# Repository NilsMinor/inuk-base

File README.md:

# Inuk base

This board is used in my open source smart garden light project. It is a 2 layer 70 mm x 100 mm design and serves as an NRF52 module carrier.
The board is powered by one 18650 rechargeable lipo and charged by an TP4056 module with a 6V solar cell. The light interface can controll up to five pwm controlled 3W LEDs.

#### Pin description

| Pin   |  Function  |                    Note |
| ----- | :--------: | ----------------------: |
| P0.26 |   LED D2   |             high active |
| P0.27 |   LED D3   |             high active |
| P0.25 | BUTTON SW2 |              low active |
| P0.06 |  UART TX   |                         |
| P0.08 |  UART RX   |                         |
| P0.07 |  UART RTS  |                         |
| P0.05 |  UART CTS  |                         |
| P0.02 |    AIN0    |     analog input - VBAT |
| P0.03 |    AIN1    |   analog input - VSOLAR |
| P0.04 |    AIN2    |            analog input |
| P0.28 |    AIN4    |     analog input - VLDR |
| P0.29 |    AIN5    |            analog input |
| P0.30 |    AIN6    |            analog input |
| P0.31 |    AIN7    |            analog input |
| P0.11 |    LIO1    |        pwm output led 1 |
| P0.12 |    LIO2    |        pwm output led 2 |
| P0.13 |    LIO3    |        pwm output led 3 |
| P0.14 |    LIO4    |        pwm output led 4 |
| P0.15 |    LIO5    |        pwm output led 5 |
| P0.16 | PIR INPUT  | pir input - high active |

#### Software

The inuk-base board is equipped with an E73-2G4M04S1B module that contains an nrf52832 SoC from nordic semiconductor. The nrf52832 bluetooth SoC comes with cortex-m4, 64K RAM and 512K ROM.

##### Note

It might happen that the E73 module comes with locked UICR. In order to unlock the flash download nrfjprog from nordic. Run the following command:

```
nrfjprog --recover
```

The output should then look like :

```
Recovering device. This operation might take 30s.
Erasing user code and UICR flash areas.
```

###### Click on the image below to see the gerber files

###### Needs to be changed for version 2

- Remove direct GND connection poligons on E73 module. The direct GND connection is difficult to solder and needs
- Add (+) symbol to battery connector
- The DCDC on the NRF52 module is not supported, this should be changed in the next version.

##View in 3D

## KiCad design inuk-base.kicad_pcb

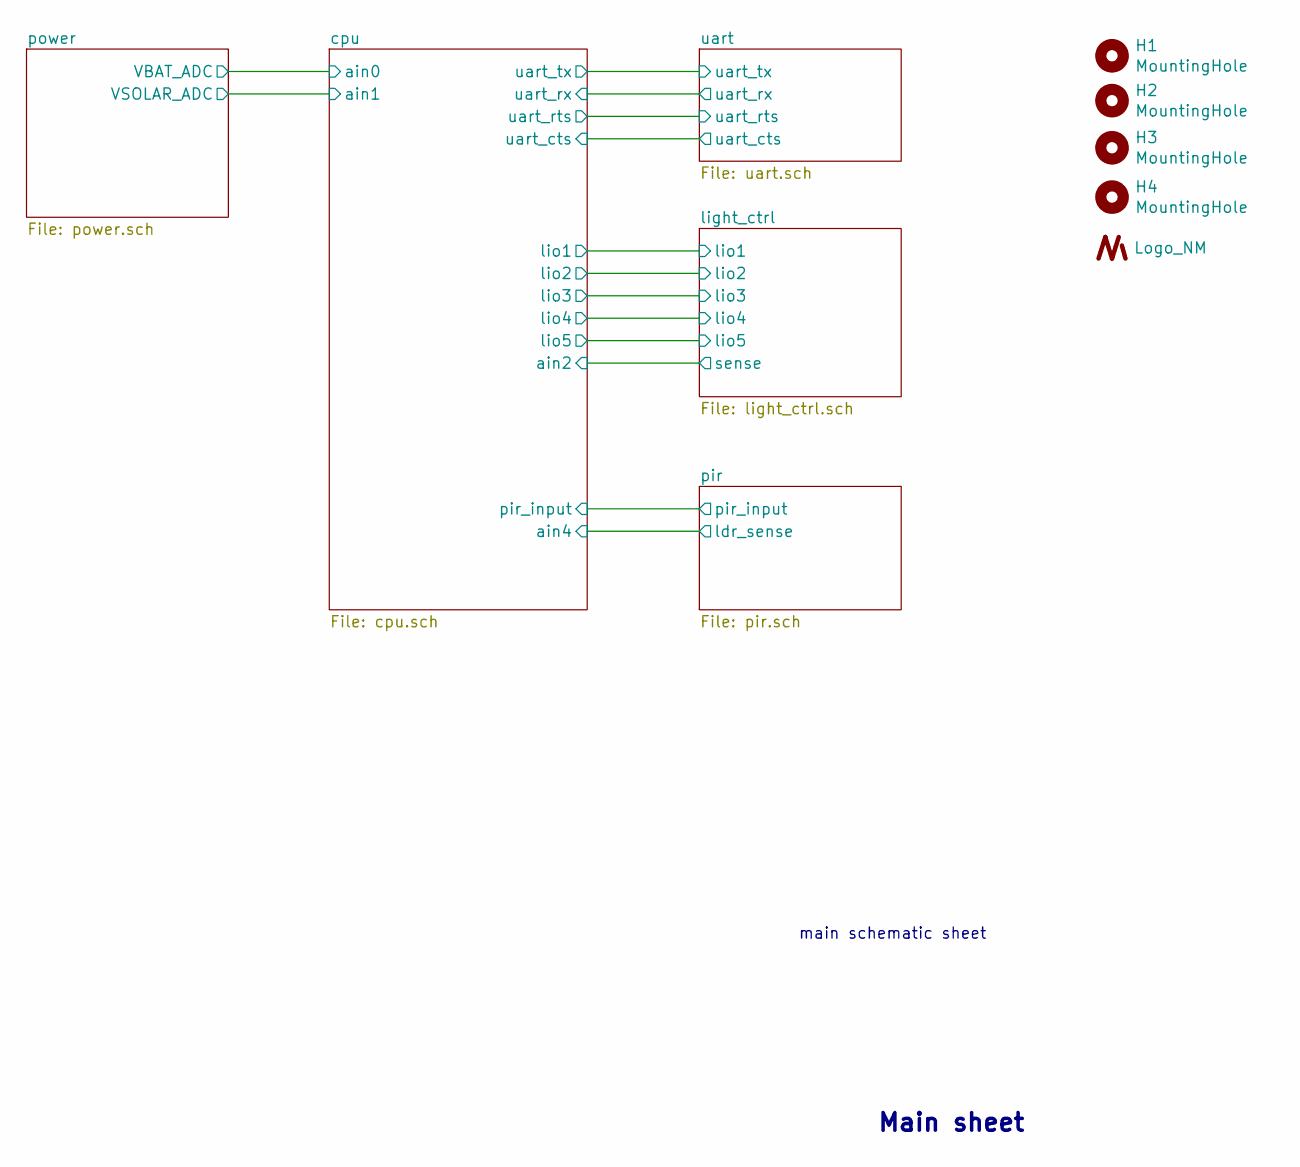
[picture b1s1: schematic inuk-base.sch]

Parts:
H1, H2, H3, H4: MountingHole; MountingHole_3.2mm_M3_Pad_Via
U4: Logo_NM

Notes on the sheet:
Main sheet
main schematic sheet

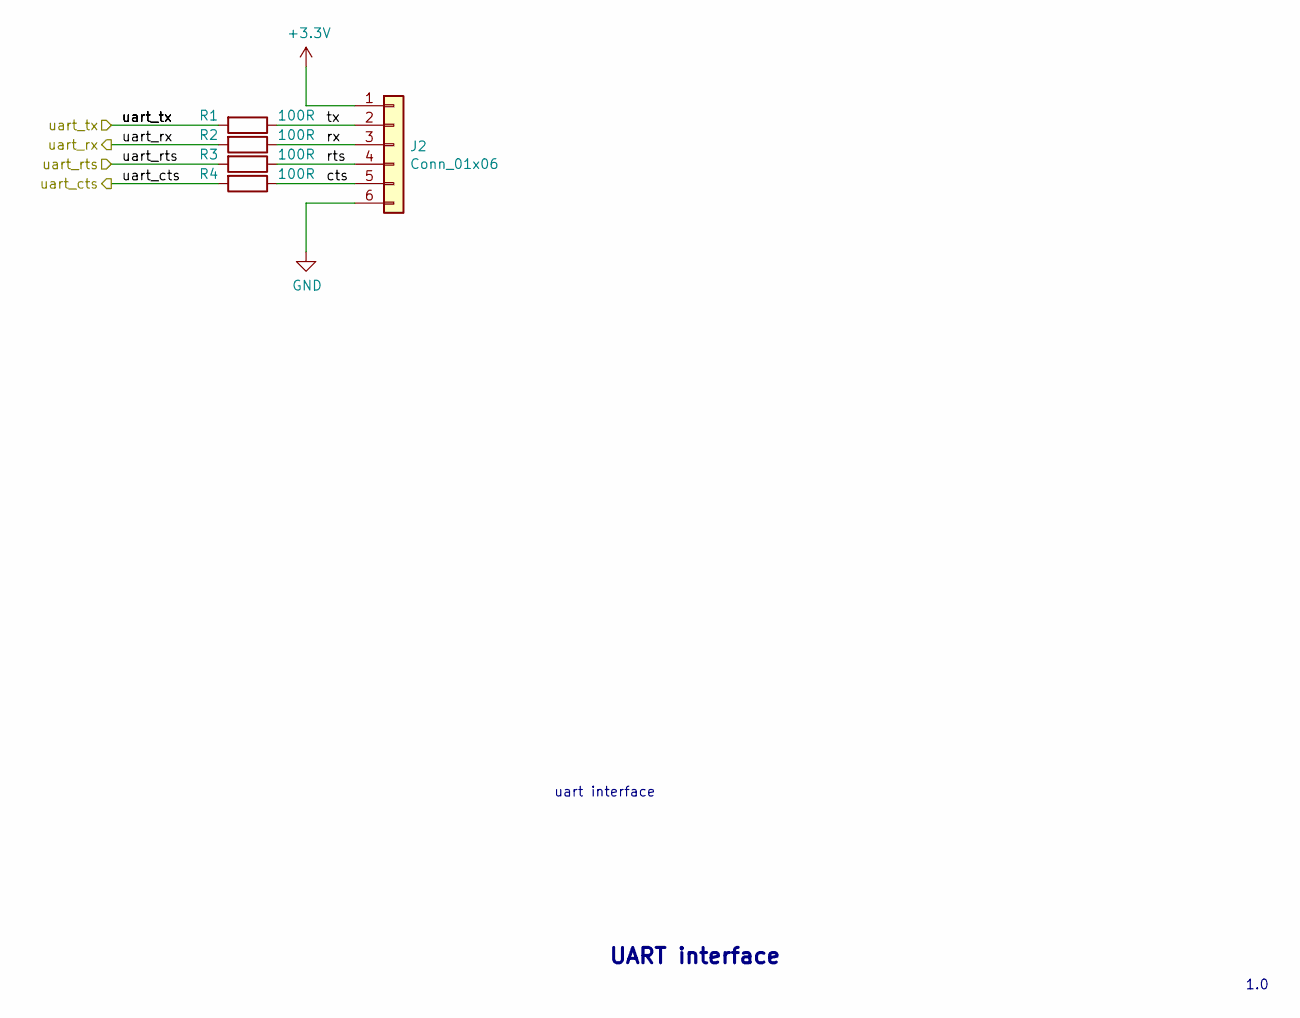
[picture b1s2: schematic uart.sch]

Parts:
J2: Conn_01x06; PinHeader_1x06_P2.54mm_Horizontal
R1, R2, R3, R4: 100R; R_0805_2012Metric_Pad1.15x1.40mm_HandSolder; MPN 0805W8F1000T5E; LCSC C17408

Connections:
/cpu/uart_cts: R4.2; also elsewhere on the board
/cpu/uart_rts: R3.2; also elsewhere on the board
/cpu/uart_rx: R2.2; also elsewhere on the board
/cpu/uart_tx: R1.2; also elsewhere on the board
/uart/cts: J2.5, R4.1
/uart/rts: J2.4, R3.1
/uart/rx: J2.3, R2.1
/uart/tx: J2.2, R1.1

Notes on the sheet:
UART interface
uart interface
1.0

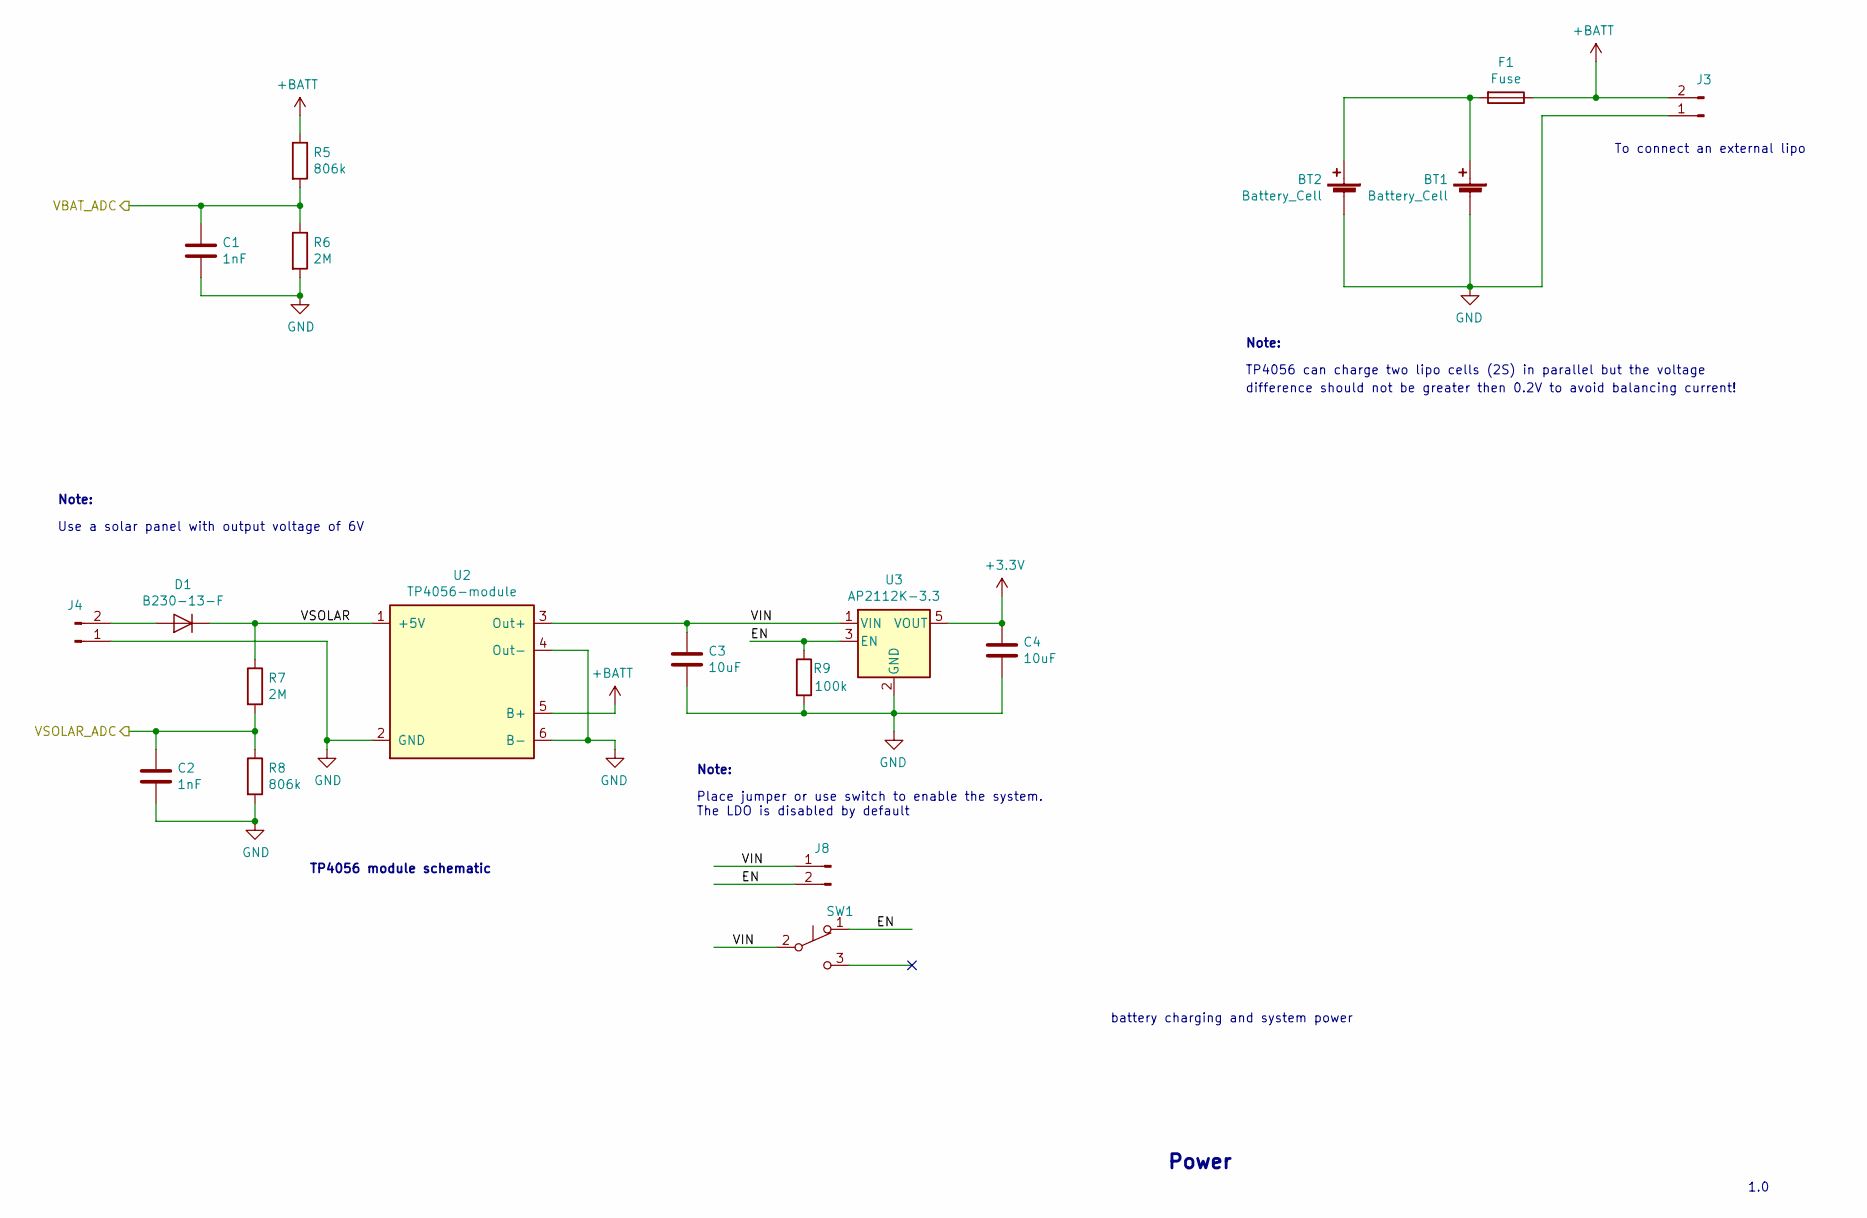
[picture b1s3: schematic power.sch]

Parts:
BT1, BT2: Battery_Cell; BatteryHolder_MPD_BH-18650-PC2
C1, C2: 1nF; C_0805_2012Metric_Pad1.15x1.40mm_HandSolder; MPN CL21B102KBCNNNC; LCSC C46653
C3, C4: 10uF; C_1210_3225Metric_Pad1.42x2.65mm_HandSolder; MPN CL31A106KBHNNNE; LCSC C13585
D1: B230-13-F; D_SMB; MPN B230-13-F; LCSC C110482
F1: Fuse; Fuse_1206_3216Metric; MPN 0466002.NRHF; LCSC C3105
J3, J4: Conn_01x02_Male; JST_PH_S2B-PH-SM4-TB_1x02-1MP_P2.00mm_Horizontal
J8: Conn_01x02_Male; PinHeader_1x02_P2.54mm_Vertical
R5, R8: 806k; R_0805_2012Metric_Pad1.15x1.40mm_HandSolder; MPN 0805W8F8063T5E; LCSC C63494
R6, R7: 2M; R_0805_2012Metric_Pad1.15x1.40mm_HandSolder; MPN 0805W8F2004T5E; LCSC C26112
R9: 100k; R_0805_2012Metric_Pad1.15x1.40mm_HandSolder; MPN 0805W8F1003T5E; LCSC C17407
SW1: SW_Push_SPDT; SW_SPDT_CK-JS102011SAQN
U2: TP4056-module
U3: AP2112K-3.3; SOT-23-5; MPN AP2112K-3.3TRG1; LCSC C51118

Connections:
+BATT: F1.1, J3.2, R5.1, U2.5 (B+); also elsewhere on the board
/power/EN: J8.2, R9.1, SW1.1 (A), U3.3 (EN)
/power/VBAT_ADC: C1.1, R5.2, R6.1; also elsewhere on the board
/power/VIN: C3.1, J8.1, SW1.2 (B), U2.3 (Out+), U3.1 (VIN)
/power/VSOLAR: D1.1 (K), R7.1, U2.1 (+5V)
/power/VSOLAR_ADC: C2.1, R7.2, R8.1; also elsewhere on the board
unnamed: BT1.1 (+), BT2.1 (+), F1.2
unnamed: D1.2 (A), J4.2

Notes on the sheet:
TP4056 can charge two lipo cells (2S) in parallel but the voltage
difference should not be greater then 0.2V to avoid balancing current!
Note:
Place jumper or use switch to enable the system. The LDO is disabled by default
TP4056 module schematic
Use a solar panel with output voltage of 6V
Power
battery charging and system power
To connect an external lipo
1.0

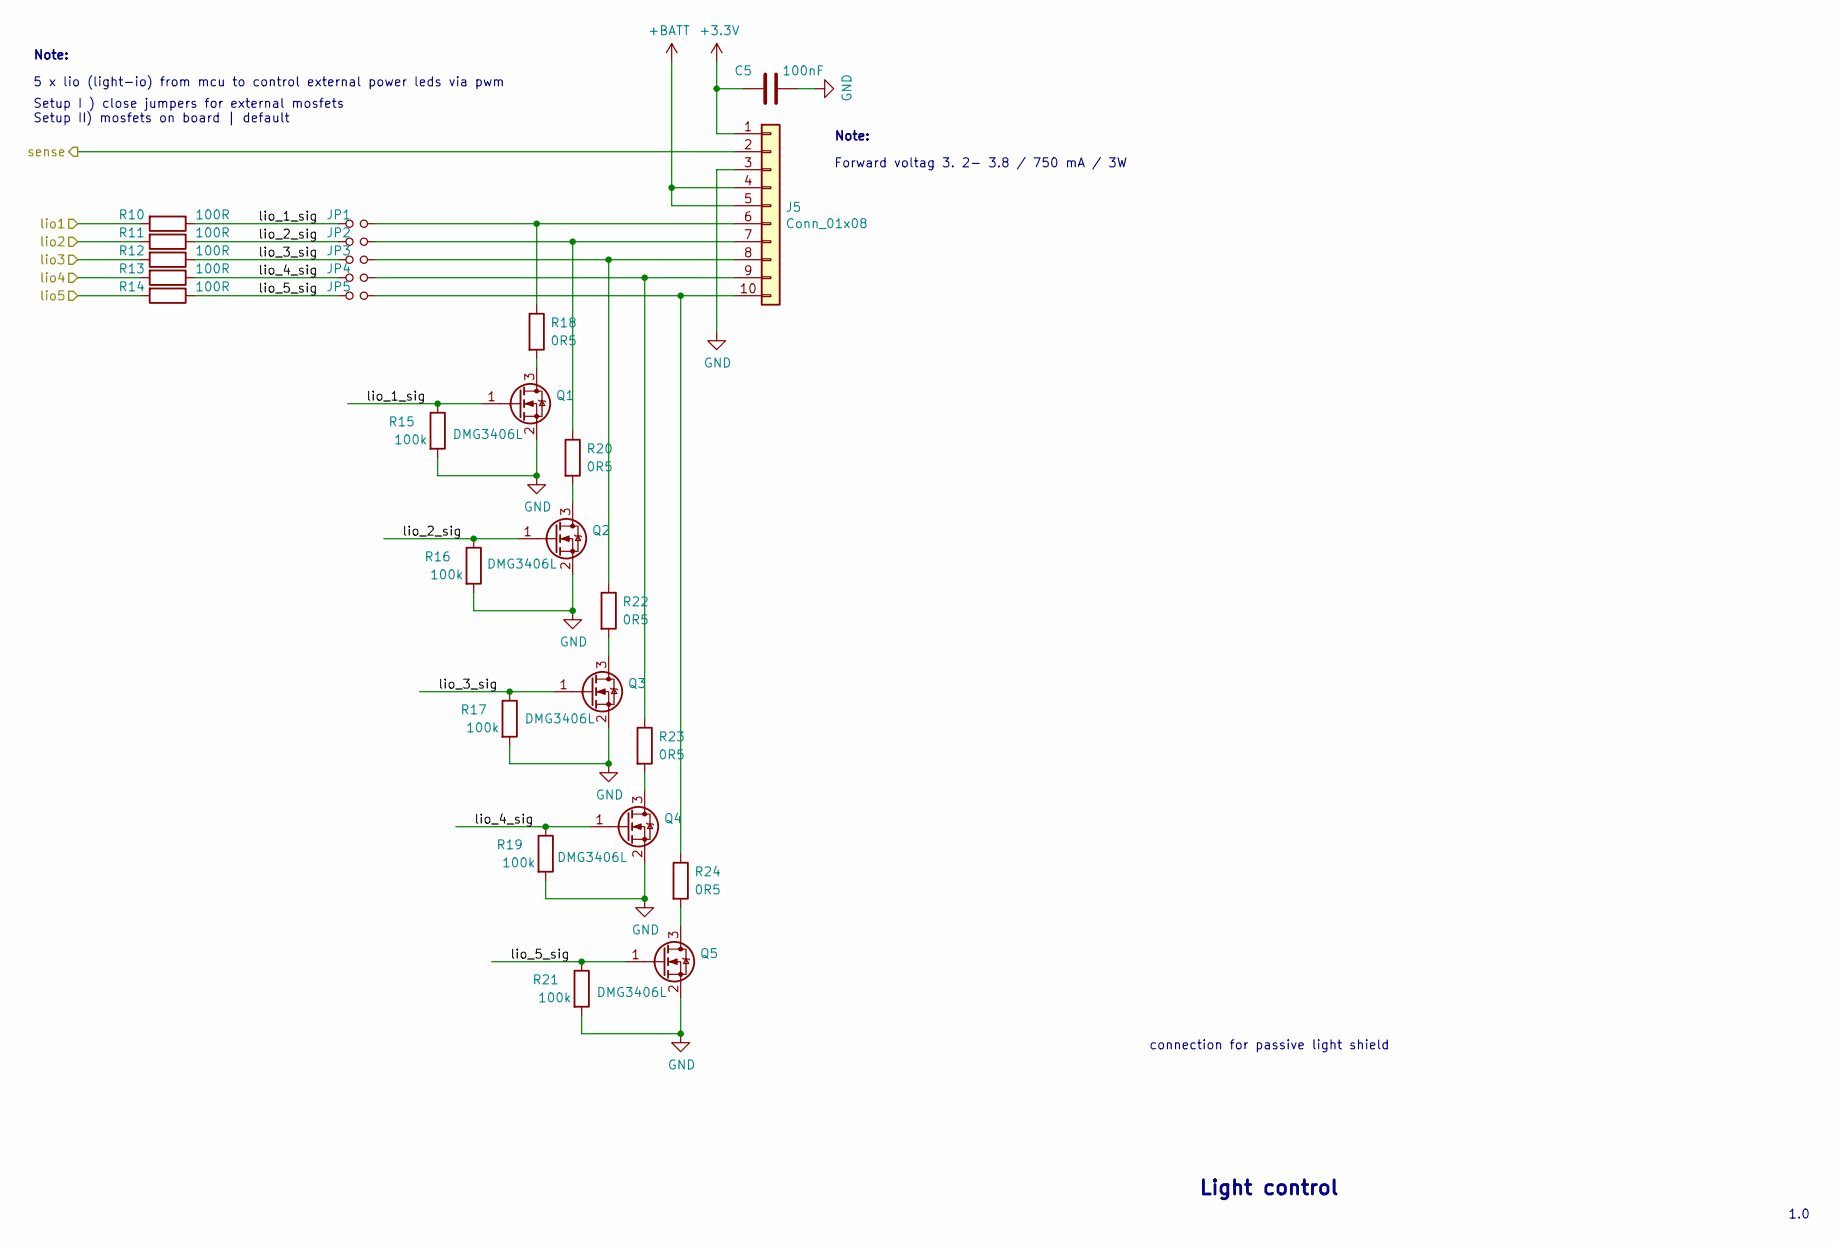
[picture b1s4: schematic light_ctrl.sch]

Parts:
C5: 100nF; C_0805_2012Metric_Pad1.15x1.40mm_HandSolder; MPN CL21B104KCFNNNE; LCSC C28233
J5: Conn_01x08; LED_shield
JP1, JP2, JP3, JP4, JP5: Jumper_NO_Small; SolderJumper-2_P1.3mm_Open_RoundedPad1.0x1.5mm
Q1, Q2, Q3, Q4, Q5: DMG3406L; SOT-23; MPN DMG3420U-7; LCSC C154722
R10, R11, R12, R13, R14: 100R; R_0805_2012Metric_Pad1.15x1.40mm_HandSolder; MPN 0805W8F1000T5E; LCSC C17408
R15, R16, R17, R19, R21: 100k; R_0805_2012Metric_Pad1.15x1.40mm_HandSolder; MPN 0805W8F1003T5E; LCSC C17407
R18, R20, R22, R23, R24: 0R5; R_1210_3225Metric_Pad1.42x2.65mm_HandSolder; MPN 1210W3F500LT5E; LCSC C21355

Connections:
+BATT: J5.4, J5.5; also elsewhere on the board
/cpu/ain2: J5.2; also elsewhere on the board
/cpu/lio1: R10.2; also elsewhere on the board
/cpu/lio2: R11.2; also elsewhere on the board
/cpu/lio3: R12.2; also elsewhere on the board
/cpu/lio4: R13.2; also elsewhere on the board
/cpu/lio5: R14.2; also elsewhere on the board
/light_ctrl/lio_1_sig: JP1.1, Q1.1 (G), R10.1, R15.1
/light_ctrl/lio_2_sig: JP2.1, Q2.1 (G), R11.1, R16.1
/light_ctrl/lio_3_sig: JP3.1, Q3.1 (G), R12.1, R17.1
/light_ctrl/lio_4_sig: JP4.1, Q4.1 (G), R13.1, R19.1
/light_ctrl/lio_5_sig: JP5.1, Q5.1 (G), R14.1, R21.1
unnamed: J5.6, JP1.2, R18.1
unnamed: J5.7, JP2.2, R20.1
unnamed: J5.8, JP3.2, R22.1
unnamed: J5.9, JP4.2, R23.1
unnamed: J5.10, JP5.2, R24.1
unnamed: Q1.3 (D), R18.2
unnamed: Q2.3 (D), R20.2
unnamed: Q3.3 (D), R22.2
unnamed: Q4.3 (D), R23.2
unnamed: Q5.3 (D), R24.2

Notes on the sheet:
5 x lio (light-io) from mcu to control external power leds via pwm
Note:
Forward voltag 3. 2- 3.8 / 750 mA / 3W
Setup I ) close jumpers for external mosfets Setup II) mosfets on board | default
Light control
connection for passive light shield
1.0

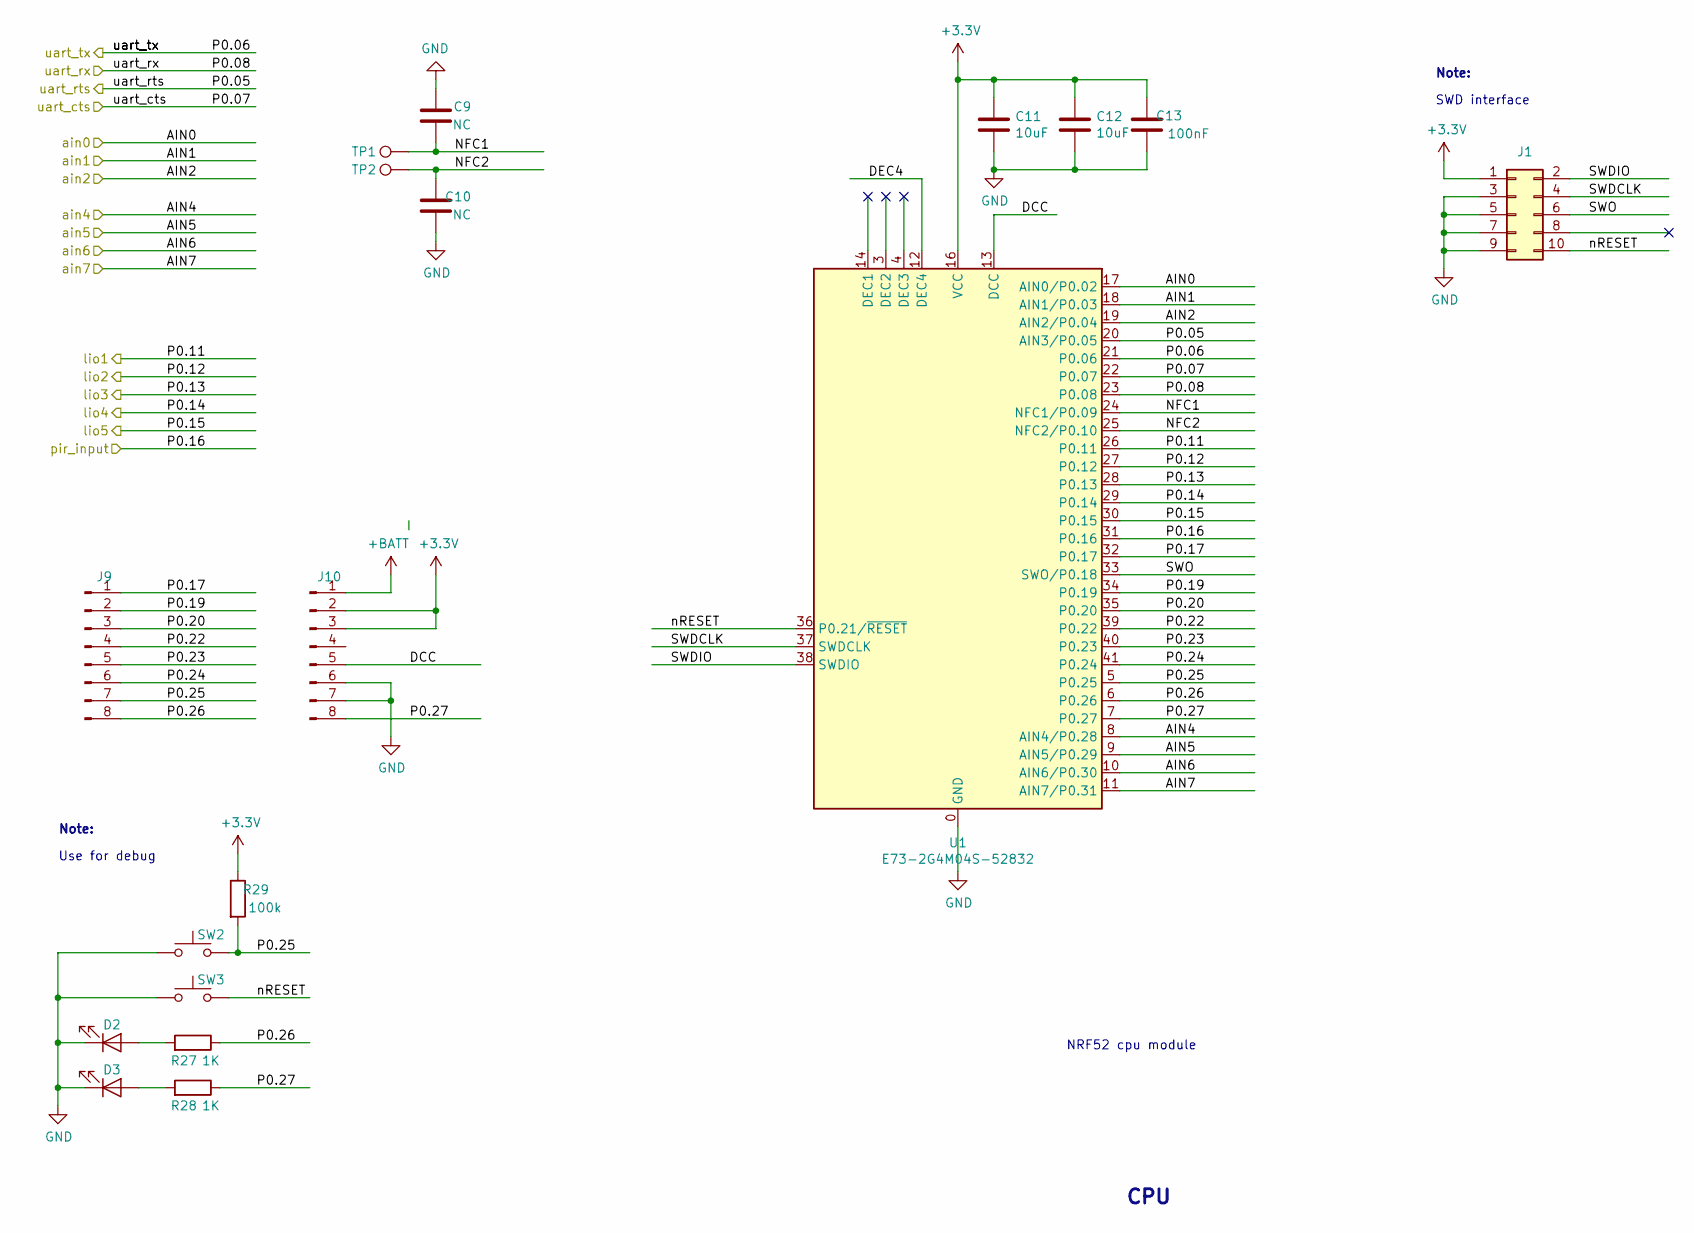
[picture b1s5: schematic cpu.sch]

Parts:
C9, C10: NC; C_0603_1608Metric
C11, C12: 10uF; C_1210_3225Metric_Pad1.42x2.65mm_HandSolder
C13: 100nF; C_0805_2012Metric_Pad1.15x1.40mm_HandSolder
D2, D3: LED; LED_0603_1608Metric_Pad1.05x0.95mm_HandSolder
J1: Conn_02x05_Odd_Even; PinHeader_2x05_P1.27mm_Vertical_SMD
J9, J10: Conn_01x08_Male; PinHeader_1x08_P2.54mm_Vertical_SMD_Pin1Left
R27, R28: 1K; R_0805_2012Metric_Pad1.15x1.40mm_HandSolder
R29: 100k; R_0805_2012Metric_Pad1.15x1.40mm_HandSolder
SW2, SW3: SW_Push; Panasonic_EVQPUL_EVQPUC
TP1, TP2: TestPoint; TestPoint_Pad_D1.5mm
U1: E73-2G4M04S-52832; E73-2G4M04S

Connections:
+BATT: J10.1; also elsewhere on the board
/cpu/AIN6: J10.4, U1.10 (AIN6/P0.30)
/cpu/DCC: J10.5, U1.13 (DCC)
/cpu/DEC4: U1.12 (DEC4)
/cpu/NFC1: C9.2, TP1.1, U1.24 (NFC1/P0.09)
/cpu/NFC2: C10.2, TP2.1, U1.25 (NFC2/P0.10)
/cpu/P0.17: J9.1, U1.32 (P0.17)
/cpu/P0.19: J9.2, U1.34 (P0.19)
/cpu/P0.20: J9.3, U1.35 (P0.20)
/cpu/P0.22: J9.4, U1.39 (P0.22)
/cpu/P0.23: J9.5, U1.40 (P0.23)
/cpu/P0.24: J9.6, U1.41 (P0.24)
/cpu/P0.25: J9.7, R29.2, SW2.2, U1.5 (P0.25)
/cpu/P0.26: J9.8, R27.1, U1.6 (P0.26)
/cpu/P0.27: J10.8, R28.1, U1.7 (P0.27)
/cpu/SWDCLK: J1.4, U1.37 (SWDCLK)
/cpu/SWDIO: J1.2, U1.38 (SWDIO)
/cpu/SWO: J1.6, U1.33 (SWO/P0.18)
/cpu/ain2: U1.19 (AIN2/P0.04); also elsewhere on the board
/cpu/ain4: U1.8 (AIN4/P0.28); also elsewhere on the board
/cpu/lio1: U1.26 (P0.11); also elsewhere on the board
/cpu/lio2: U1.27 (P0.12); also elsewhere on the board
/cpu/lio3: U1.28 (P0.13); also elsewhere on the board
/cpu/lio4: U1.29 (P0.14); also elsewhere on the board
/cpu/lio5: U1.30 (P0.15); also elsewhere on the board
/cpu/nRESET: J1.10, SW3.2, U1.36 (P0.21/~RESET)
/cpu/pir_input: U1.31 (P0.16); also elsewhere on the board
/cpu/uart_cts: U1.22 (P0.07); also elsewhere on the board
/cpu/uart_rts: U1.20 (AIN3/P0.05); also elsewhere on the board
/cpu/uart_rx: U1.23 (P0.08); also elsewhere on the board
/cpu/uart_tx: U1.21 (P0.06); also elsewhere on the board
/power/VBAT_ADC: U1.17 (AIN0/P0.02); also elsewhere on the board
/power/VSOLAR_ADC: U1.18 (AIN1/P0.03); also elsewhere on the board
unnamed: D2.2 (A), R27.2
unnamed: D3.2 (A), R28.2

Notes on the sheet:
SWD interface
Note:
Use for debug
CPU
NRF52 cpu module

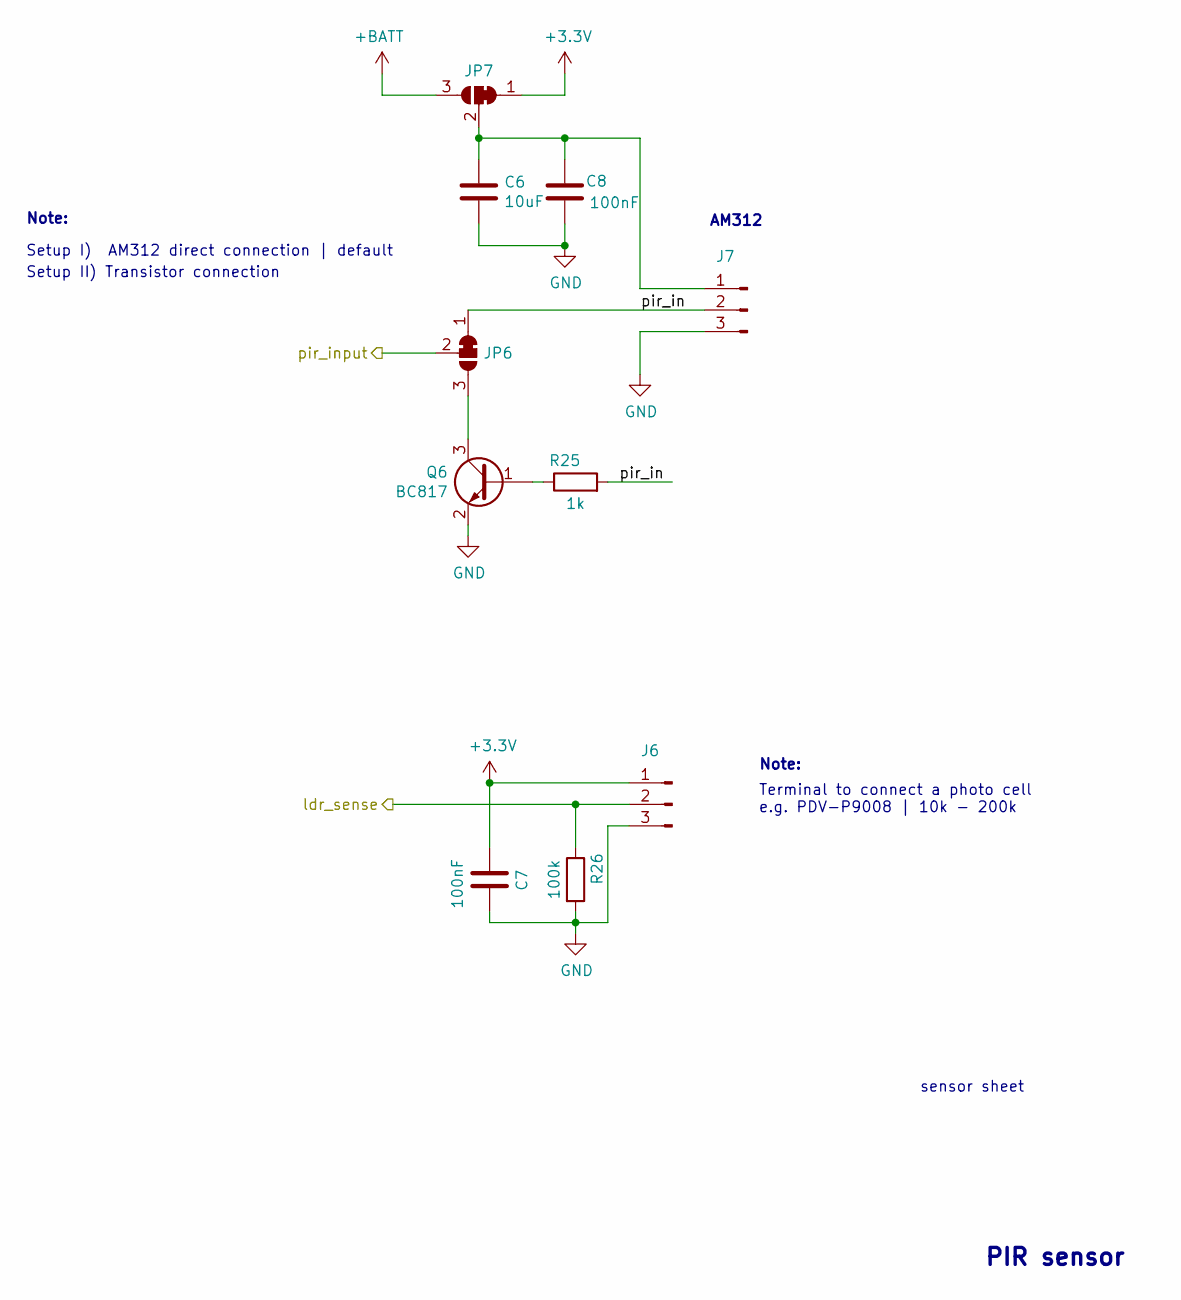
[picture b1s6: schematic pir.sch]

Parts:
C6: 10uF; C_1210_3225Metric_Pad1.42x2.65mm_HandSolder
C7, C8: 100nF; C_0805_2012Metric_Pad1.15x1.40mm_HandSolder
J6, J7: Conn_01x03_Male; PinHeader_1x03_P2.54mm_Vertical
JP6, JP7: SolderJumper_3_Bridged12; SolderJumper-3_P1.3mm_Bridged12_RoundedPad1.0x1.5mm
Q6: BC817; SOT-23
R25: 1k; R_0805_2012Metric_Pad1.15x1.40mm_HandSolder
R26: 100k; R_0805_2012Metric_Pad1.15x1.40mm_HandSolder

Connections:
+BATT: JP7.3 (B); also elsewhere on the board
/cpu/ain4: J6.2, R26.1; also elsewhere on the board
/cpu/pir_input: JP6.2 (C); also elsewhere on the board
/pir/pir_in: J7.2, JP6.1 (A), R25.2
unnamed: C6.1, C8.2, J7.1, JP7.2 (C)
unnamed: JP6.3 (B), Q6.3 (C)
unnamed: Q6.1 (B), R25.1

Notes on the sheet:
Setup I) AM312 direct connection | default
Note:
Setup II) Transistor connection
AM312
Terminal to connect a photo cell e.g. PDV-P9008 | 10k - 200k
PIR sensor
sensor sheet

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
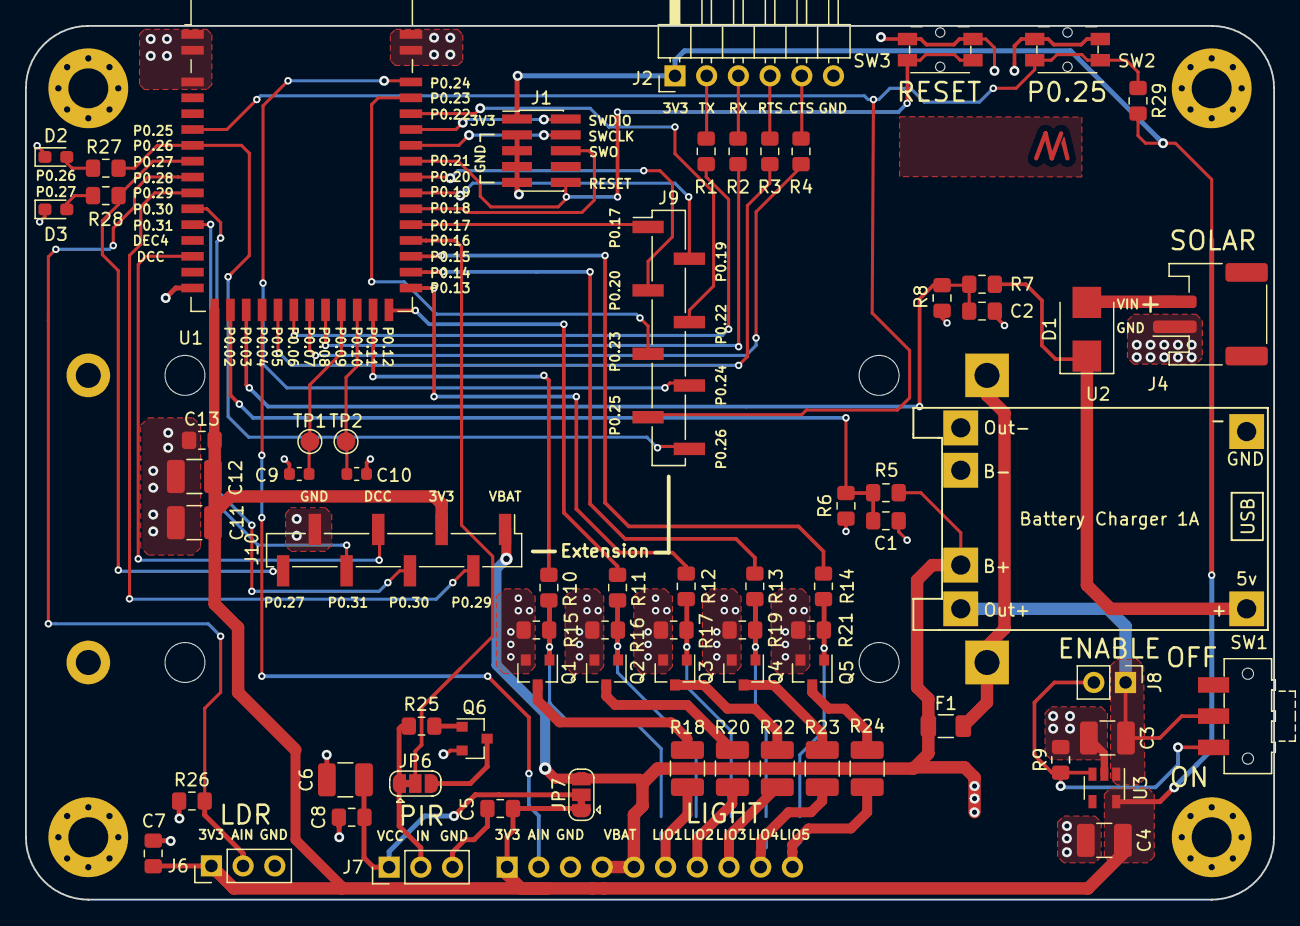
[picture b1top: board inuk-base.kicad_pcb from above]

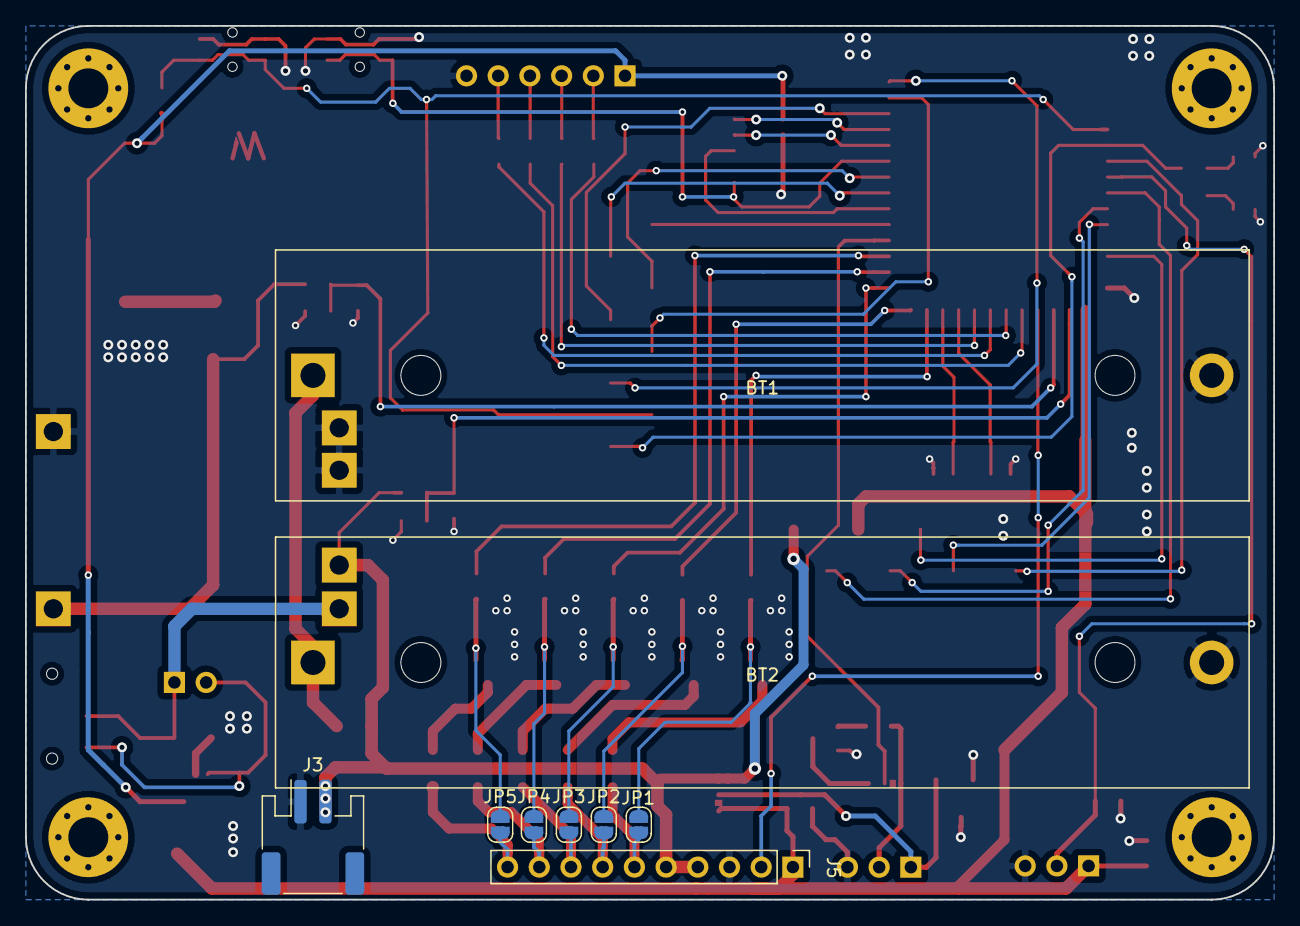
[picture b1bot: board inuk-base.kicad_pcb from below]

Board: 2 copper layers, 100.0 x 70.0 mm, 84 parts (9 on the bottom side), 66 nets.

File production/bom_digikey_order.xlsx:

Comment | Designator | Footprint | Count | MPN
Fuse | F1 | Fuse:Fuse_1206_3216Metric | 1 | 0466002.NRHF
100R | R1,R2,R3,R4,R10,R11,R12,R13,R14 | Resistor_SMD:R_0805_2012Metric_Pad1.15x1.40mm_HandSolder | 9 | 0805W8F1000T5E
1k | R28,R27,R25 | Resistor_SMD:R_0805_2012Metric_Pad1.15x1.40mm_HandSolder | 3 | 0805W8F1001T5E
100k | R9,R16,R17,R19,R21,R15,R29,R26 | Resistor_SMD:R_0805_2012Metric_Pad1.15x1.40mm_HandSolder | 8 | 0805W8F1003T5E
2M | R6,R7 | Resistor_SMD:R_0805_2012Metric_Pad1.15x1.40mm_HandSolder | 2 | 0805W8F2004T5E
806k | R5,R8 | Resistor_SMD:R_0805_2012Metric_Pad1.15x1.40mm_HandSolder | 2 | 0805W8F8063T5E
0R5 | R24,R23,R22,R20,R18 | Resistor_SMD:R_1210_3225Metric_Pad1.42x2.65mm_HandSolder | 5 | 1210W3F500LT5E
LED | D3,D2 | LED_SMD:LED_0603_1608Metric_Pad1.05x0.95mm_HandSolder | 2 | 19-217/GHC-YR1S2/3T
AP2112K-3.3 | U3 | Package_TO_SOT_SMD:SOT-23-5 | 1 | AP2112K-3.3TRG1
B230-13-F | D1 | Diode_SMD:D_SMB | 1 | B230-13-F
1nF | C1,C2 | Capacitor_SMD:C_0805_2012Metric_Pad1.15x1.40mm_HandSolder | 2 | CL21B102KBCNNNC
100nF | C5,C13,C8,C7 | Capacitor_SMD:C_0805_2012Metric_Pad1.15x1.40mm_HandSolder | 4 | CL21B104KCFNNNE
10uF | C3,C4,C11,C12,C6 | Capacitor_SMD:C_1210_3225Metric_Pad1.42x2.65mm_HandSolder | 5 | CL31A106KBHNNNE
DMG3406L | Q2,Q3,Q4,Q5,Q1 | Package_TO_SOT_SMD:SOT-23 | 5 | DMG3420U-7
Battery_Cell | BT1,BT2 | Battery:BatteryHolder_MPD_BH-18650-PC2 | 1 | BK-18650-PC2
Conn_02x05_Odd_Even | J1 | Connector_PinHeader_1.27mm:PinHeader_2x05_P1.27mm_Vertical_SMD | 1 | FTSH-105-01-L-DV
Conn_01x06 | J2 | Connector_PinHeader_2.54mm:PinHeader_1x06_P2.54mm_Horizontal | 1 | 61301011121
Conn_01x02_Male | J4,J3 | Connector_JST:JST_PH_S2B-PH-SM4-TB_1x02-1MP_P2.00mm_Horizontal | 2 | S2B-PH-SM4-TB
Conn_01x08 | J5 | Custom:LED_shield | 1 | 61301211121
Conn_01x02_Male | J8 | Connector_PinHeader_2.54mm:PinHeader_1x02_P2.54mm_Vertical | 1 | 61301211121
Conn_01x08_Male | J9,J10 | Connector_PinHeader_2.54mm:PinHeader_1x08_P2.54mm_Vertical_SMD_Pin1Left | 1 | 61001618221 | 16 pin MPN selected to break
Conn_01x03_Male | J7,J6 | Connector_PinHeader_2.54mm:PinHeader_1x03_P2.54mm_Vertical | 2
SW_Push_SPDT | SW1 | Button_Switch_SMD:SW_SPDT_CK-JS102011SAQN | 1 | JS102011SAQN
SW_Push | SW3,SW2 | Button_Switch_SMD:Panasonic_EVQPUL_EVQPUC | 2 | EVQ-PUC02K

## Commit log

2020-03-22 added TP4056 module
2020-03-22 pcb layout
2020-03-31 created light control schematic
2020-04-02 layout
2020-04-12 added more circuit parts + new step files
2020-04-13 started pcb routing
2020-04-14 more layout + resized pcb to 100 x 80
2020-04-15 changed pcb size to 100 x 70 and made progress on layout
2020-04-17 layout and more silk informations
2020-04-19 finished layout, created production files and added readme
2020-04-19 changed images in readme
2020-04-21 added bom
2020-05-12 added README with programming info
2020-05-15 pinout in readme
2020-05-23 more pin info
